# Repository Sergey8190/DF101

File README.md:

"Учебная практика по получению первичных профессиональных умений и навыков"

Задание 2: построить 3D модель небольшого объекта (например, буквы) с использованием метода твердотельного моделирования. Размеры: до 30x30x20 мм. Сохранить модель в формате STL для 3D печати. Разбить STL на множество слоев с помощью программы Cura. Сохранить слои в формате GCODE. 

 Объяснение: на данном скриншоте представлена построенная 3D модель буквы "Н" с использованием метода твердотельного моделирования. Размером: 30x30x20 мм.

 Объяснение: на данном скриншоте представлена 3D модель после разбития на множество слоев с помощью программы Cura.
Задание 3: подготовить в любой программе для рисования векторной графики (Inkscape, CorelDraw, Illustrator) файл в формате DXF для лазерной резки (цвета, толщина контура). Файл должен содержать чертеж плоских деталей коробки с пазами для плотной посадки. Размеры коробки до 60x60x60 мм.  Материал: фанера (толщина 3 мм). Разместить все файлы в репозитории DF101.

 Объяснение: на данном скриншоте представленфайл в формате DXF для лазерной резки. На нем изображен чертеж плоских деталей коробки с пазами для плотной посадки. Размеры коробки 60x60x60 мм.

Файлы проекта "Пульт управления роботом"

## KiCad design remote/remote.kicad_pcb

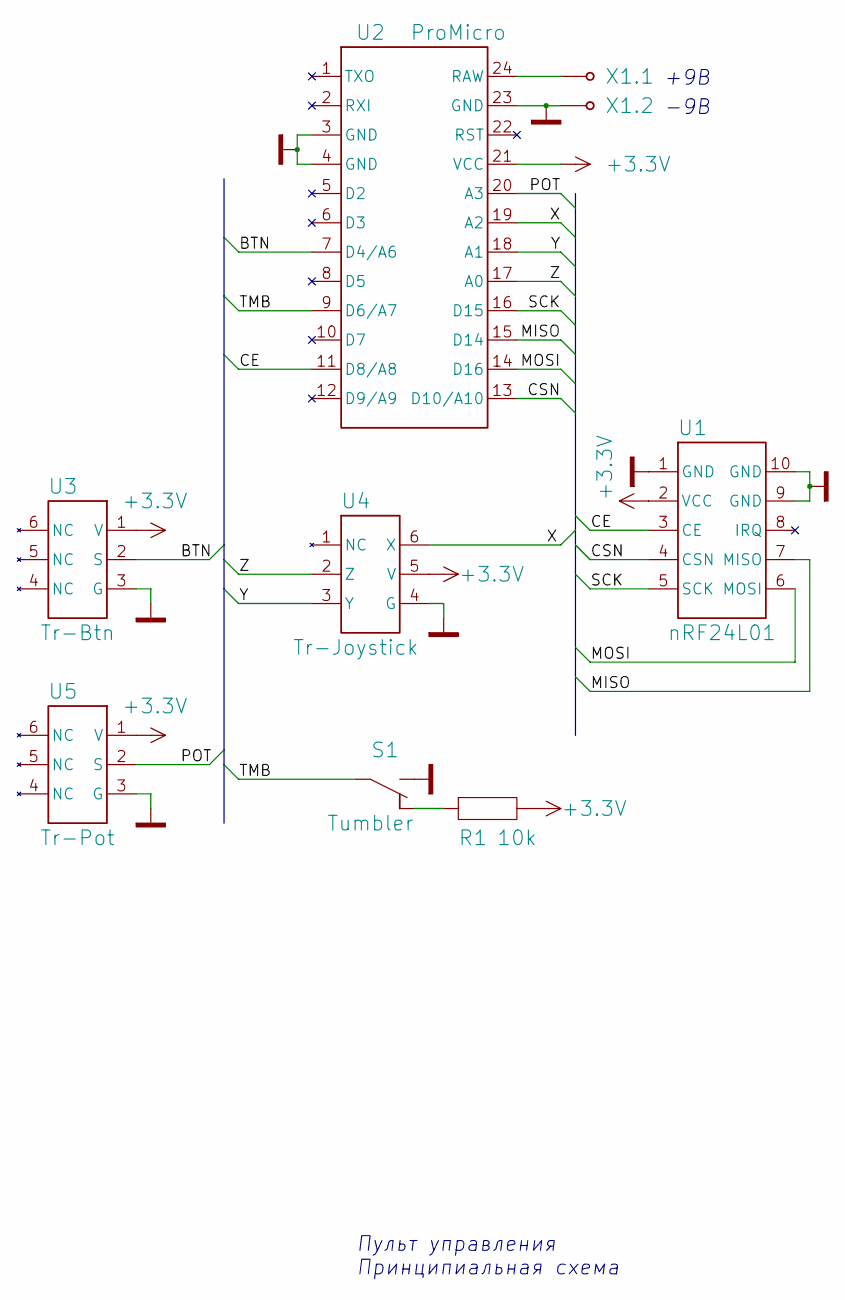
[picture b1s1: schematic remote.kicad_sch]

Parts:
R1: 10k; MF-0,25
S1: Tumbler; MTS-102
U1: nRF24L01
U2: ProMicro
U3: Tr-Btn; Troyka
U4: Tr-Joystick; Troyka
U5: Tr-Pot; Troyka
X1.1, X1.2: ConnH; CP-0,7-1.5

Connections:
+3.3V: R1.2, U1.2 (VCC), U2.21 (VCC), U3.1 (V), U4.5 (V), U5.1 (V)
/BTN: U2.7 (D4/A6), U3.2 (S)
/CE: U1.3 (CE), U2.11 (D8/A8)
/CSN: U1.4 (CSN), U2.13 (D10/A10)
/MISO: U1.7 (MISO), U2.15 (D14)
/MOSI: U1.6 (MOSI), U2.14 (D16)
/POT: U2.20 (A3), U5.2 (S)
/SCK: U1.5 (SCK), U2.16 (D15)
/TMB: S1.1, U2.9 (D6/A7)
/X: U2.19 (A2), U4.6 (X)
/Y: U2.18 (A1), U4.3 (Y)
/Z: U2.17 (A0), U4.2 (Z)
GND: S1.2, U1.1 (GND), U1.9 (GND), U1.10 (GND), U2.3 (GND), U2.4 (GND), U2.23 (GND), U3.3 (G), U4.4 (G), U5.3 (G), X1.2.1
unnamed: R1.1, S1.3
unnamed: U2.24 (RAW), X1.1.1

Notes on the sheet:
-9В
+9В
Пульт управления Принципиальная схема

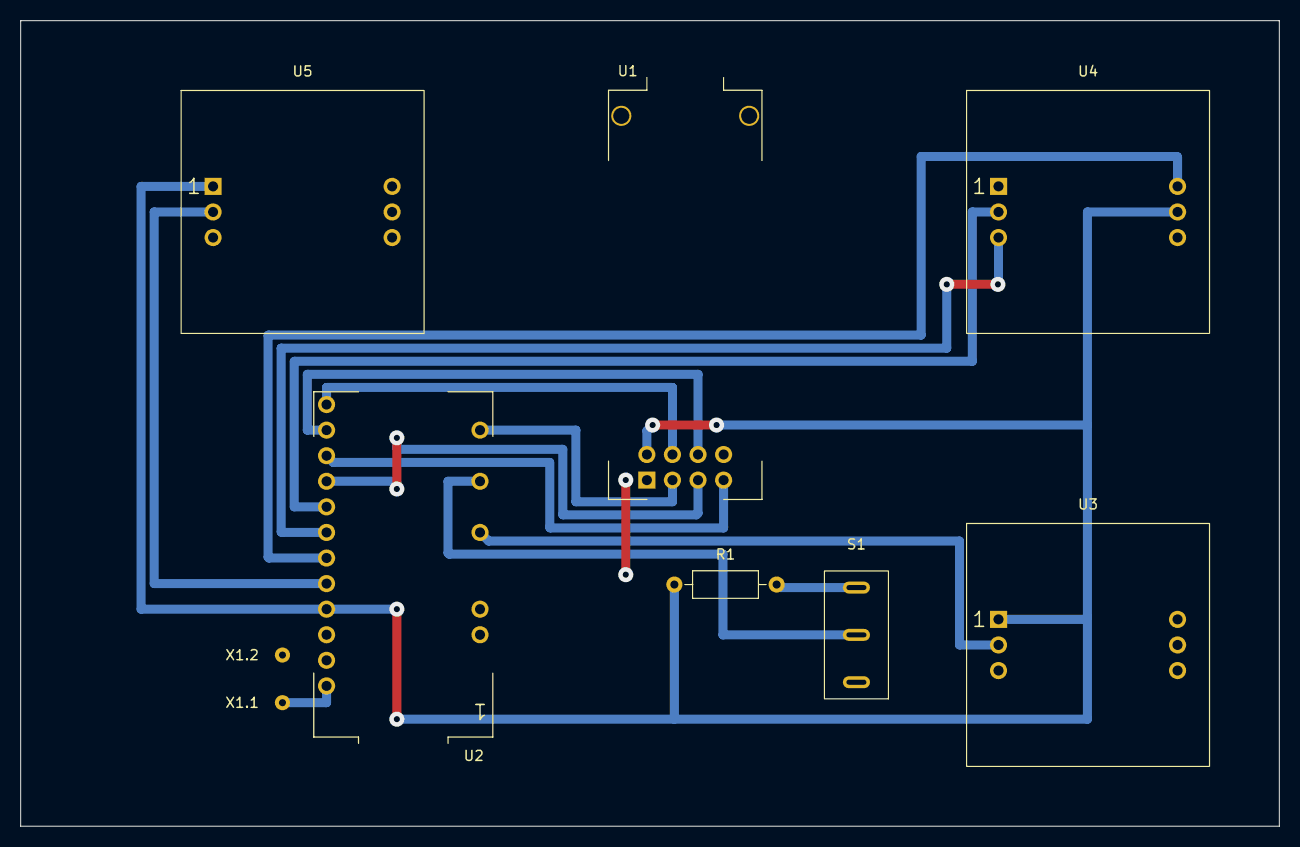
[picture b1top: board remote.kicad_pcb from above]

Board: 2 copper layers, 125.0 x 80.0 mm, 9 parts (0 on the bottom side), 15 nets.
